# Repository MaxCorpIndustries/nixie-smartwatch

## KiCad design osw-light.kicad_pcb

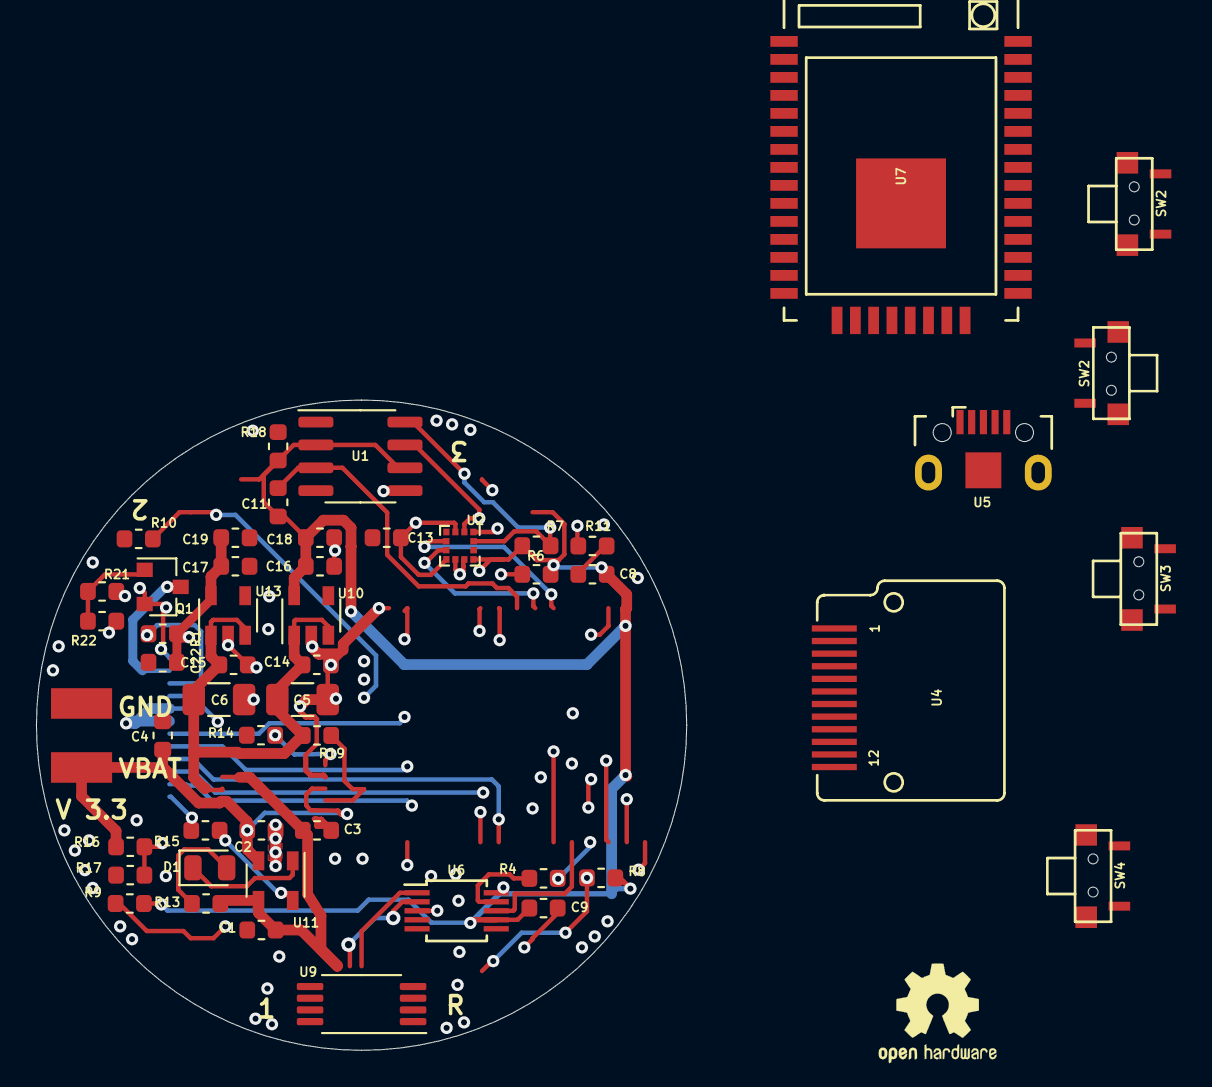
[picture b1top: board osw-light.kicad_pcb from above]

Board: 4 copper layers, 36.1 x 36.1 mm, 51 parts (0 on the bottom side), 35 nets.

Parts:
C1, C2: 4.7uF; C_0603_1608Metric
C3, C4, C8, C9, C11, C13, C14, C15, C18, C19, C22: 0.1u; C_0603_1608Metric
C5, C6: 100u; C_1206_3216Metric
C16, C17: 4.7u; C_0603_1608Metric
D1: LED_Green; LED_0805_2012Metric
J1: Conn_01x02; PinHeader_1x02_P2.54mm_Vertical
Q1: 2N7002; SOT-23
R1: 22; R_0603_1608Metric
R4, R13: 470R; R_0603_1608Metric
R6, R7: 1k; R_0603_1608Metric
R8, R9, R10, R11, R17, R21: 10k; R_0603_1608Metric
R14: 510R; R_0603_1608Metric
R15: 5k; R_0603_1608Metric
R16: 200k; R_0603_1608Metric
R18: 2.2K; R_0603_1608Metric
R19: 220k; R_0603_1608Metric
R22: 1M; R_0603_1608Metric
SW2, SW2#2, SW3, SW4: SW_Push; button_side_smd
U1: DS3231MZ; SOIC-8_3.9x4.9mm_P1.27mm
U2: BMA400; LGA-12_2x2mm_P0.5mm
U4: GC9A01_IPS_display
U5: USB-OTG; USBmicro-B
U6: CH340E; MSOP-10_3x3mm_P0.5mm
U7: ttgo-32-micro
U9: TPS2115A; TSSOP-8_4.4x3mm_P0.65mm
U10, U13: XC6209; SOT-23-5
U11: MCP73831T-2ACI_OT; SOT-23-5

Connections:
+3V3: C8.1, C9.1, C11.1, C13.1, C16.1, C18.1, R6.1, R7.1, R8.1, R9.1, R18.2, U1.2, U1.6, U2.3, U2.7, U2.10, U6.7, U6.10, U7.2, U10.5
/3V3_2: C17.1, C19.1, C22.1, R1.1, U4.4, U13.5
/BTN2: R10.1, U7.18
/BTN3: R11.1, U7.16
/B_MON: R16.2, R17.1, U7.10
/D_N: U5.4, U6.2
/D_P: U5.3, U6.1
/EN: R8.2, SW4.2, U7.3
/FLASH: R9.2, U7.25
/IO34: U2.5, U7.6
/IO35: U2.6, U7.7
/LEDK: Q1.3, U4.2
/MOSI: U4.10, U7.37
/PIN_LED: R21.2, U7.17
/RTC_INT: R18.1, U1.3, U7.8
/RX: U6.8, U7.34
/SCK: U4.9, U7.30
/SCL: R7.2, U1.8, U2.12, U7.36
/SDA: R6.2, U1.7, U2.2, U7.33
/STAT_PWR: R19.2, U7.23, U9.1
/TFT_CS: U4.8, U7.29
/TFT_DC: U4.7, U7.14
/TFT_RST: U4.11, U7.9
/TX: R4.2, U7.35
/VBAT: C2.1, C4.1, J1.1, R16.1, U9.2, U9.8, U11.3
/VBUS: C1.2, C3.1, R13.2, U5.5, U9.6, U11.4
/VCC: C5.1, C6.1, C14.1, C15.1, R19.1, U9.7, U10.1, U10.3, U13.1, U13.3
GND: C1.1, C2.2, C3.2, C4.2, C5.2, C6.2, C8.2, C9.2, C11.2, C13.2, C14.2, C15.2, C16.2, C17.2, C18.2, C19.2, C22.2, J1.2, Q1.2, R10.2, R11.2, R14.2, R15.2, R17.2, R22.1, SW4.1, U1.5, U2.1, U2.8, U2.9, U4.1, U4.5, U4.6, U4.12, U5.1, U6.3, U7.1, U7.15, U7.38, U9.3, U9.5, U10.2, U11.2, U13.2
unnamed: D1.1, U11.1
unnamed: D1.2, R13.1
unnamed: Q1.1, R21.1, R22.2
unnamed: R1.2, U4.3
unnamed: R4.1, U6.9
unnamed: R14.1, U9.4
unnamed: R15.1, U11.5

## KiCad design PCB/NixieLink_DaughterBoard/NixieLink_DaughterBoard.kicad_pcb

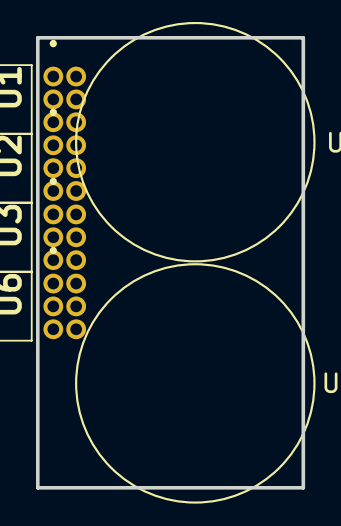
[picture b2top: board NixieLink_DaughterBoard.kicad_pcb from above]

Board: 2 copper layers, 14.8 x 25.0 mm, 6 parts (0 on the bottom side), 7 nets, no tracks yet.

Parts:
U1, U2, U3, U6: 20021112-00006T4LF; 2002111200006T4LF
U4, U5: IN-16-Correct; IN-16

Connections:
unnamed: U1.2, U4.2 ("1")
unnamed: U1.4, U4.3 ("7")
unnamed: U1.6, U4.4 ("3")
unnamed: U1.5, U4.6 ("4")
unnamed: U1.3, U4.7 ("5")
unnamed: U1.1, U4.8 ("6")
unnamed: U4.1 (Anode), U5.1 (Anode)

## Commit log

2023-08-02 first commit + CAD models
    Added CAD files for V1 nixie watch, this includes
    - chassis
    - lid
    - 1.25 mm acrylic pane
    - IN 16 nixie tubes
    - Daughter board PCB
2023-08-03 Updated CAD and rough PCB in KiCAD
2023-08-03 Autosave
2023-08-07 Updated to V2 chassis, that allows a better closure around the PCB
2023-08-08 Updated Chassis
2023-08-08 Added PCB daughter board pins
2023-08-08 Updated PCB and removed unneeded models.
2023-08-10 Updated CAD
2023-08-10 Added water entry prevention lip
2023-08-11 Saved CAD
2023-08-15 Updated 3D model
2023-08-18 Added drawing, battery, and buttons on CAD model
2023-08-19 Added some renders
2023-08-21 Added engineering drawing
2023-08-21 Drawing Updates
2023-08-25 Added modern CAD files
2023-08-25 Updated File structure
2023-08-25 Updated CAD and component layout diagram
2023-08-26 Updated menu layout graph
2023-08-27 updated display flowchart
2023-08-28 Added packngo zip
2023-08-28 Closed solidworks
2023-09-07 Added Screens + Settings
